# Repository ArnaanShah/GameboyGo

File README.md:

# Gameboy Go 🎮

A handheld console for playing retro games with an interesting sliding mechanism. The console has aspects of a Gameboy and a PSP Go, which led to the name. I made this as a part of [Hackclub's Stasis](https://stasis.hackclub.com) program which funds custom hardware projects. I decided to make a game console because I thought it could teach me a lot of new things and allow me to explore topics I'd been interested in for a long time. It also seemed like it would be very fun, and I could continue using it after I finished the build.

## Setup
### The steps you'll need to get up and running with a Gameboy Go

1. Order all the parts based off the BOM
2. Solder your electrical components onto your PCB based on the models and schematics
3. Download RetroPie using the raspberry pi imager and put it on a SD card into the raspberry pi
4. Use a computer and the command line to get setup and change the configuration files according to the instructions
5. Unplug all components 
6. Assemble the bottom half of the case in this order - Bottom, PCB, Middle, Buttons, Top
7. Assemble the top half of the case containing the screen in this order - Bottom, Display, Top
8. Route the wires to connect the screen to the main case
9. Plug it into a power source
10. You're done!

## Features
### What this console can do and what it's made of

- 2 part sliding black and yellow case
- 3.5 inch screen
- 15 buttons including face buttons, a DPAD, shoulder buttons, menu buttons, and volume controls
- 3.5mm audio jack for headphones

## CAD 
### The 3d model of the case and components

I modeled in fusion 360 but I also got a lot of models for components online. In total, this will require 21 screws and 17 nuts. 7 will be used to hold parts of the case together, 2 will be used for the PCB, and 8 will be used for the hinges. There are 3 separate parts in the main case. The bottom, the middle, and the top. The other portion has 2 parts to sandwich the screen so just a top and bottom. The parts are held together by 4 hinges. The wires for the screen are routed through the back and there is also a hole there for power. 

Images:

## PCB 
### Details about the PCB I made

I made my PCB in KiCad. I used it before for other projects so I already knew the basics. My schematic was pretty simple but included things like a low-pass filter for the audio. The PCB layout was also easy to make but I just had to work around a lot of the constraints with making a PCB of this size with this many components. 

Schematic:

PCB:

3d Renders:

## Software Configuration
### How to get setup with the software and make RetroPie work with this console

There wasn't much to do on the software/programming side of this project. I had planned from the start to use an emulator called RetroPie for the console. It handles almost everything and you just need to set it up and change some things to match your console. 

In order to get RetroPie working on the Gameboy Go, you have to add audio functionality, configure the WaveShare screen, and use RetroGame for button inputs. 

First, get your screen up and running by accessing the pi from your computer and following [these instructions](https://www.waveshare.com/wiki/3.5inch_RPi_LCD_(G)#Calibrate_Resistive_Touch_Screen) from the official wiki. 

Then, add these lines to your config.txt file to get audio on the headphone jack working:
```
dtparam=audio=on

audio_pwm_mode=2
(This may be on by default but if not add it)
```

Finally, for the buttons, you need to [install RetroGame](https://learn.adafruit.com/retro-gaming-with-raspberry-pi/adding-controls-software) from Adafruit in order to convert button inputs from GPIO pins to key presses. Then, you need to edit the retrogame.cfg file to match the one provided in the configuration folder. 

That should be everything needed to get the console running nicely. 

## BOM
### Bill of materials needed with names, links, and quantities

| Name | Amount | Link |
|---|---|---|
| Raspberry pi Zero 2 w | 1 | [Raspberry pi](https://www.raspberrypi.com/products/raspberry-pi-zero-2-w/?variant=raspberry-pi-zero-2-w) |
| 3.5inch RPi LCD (G) | 1 | [WaveShare](https://www.waveshare.com/3.5inch-rpi-lcd-g.htm?srsltid=AfmBOopoyxl4aeTF2s5BtMy4MCuqwqXwdewwnlaeLHAK1Bwd1KD4Ym0p) |
| 6mm Push Buttons | 11 | [Adafruit](https://www.adafruit.com/product/367?srsltid=AfmBOoqAj2fYT_9Y2s0Y7QZpG46cAeABVtzY1UmmWIn-tXu1GYy3M0Tw) |
| 270 ohm resistors | 2 | [MicroCenter](https://www.microcenter.com/product/689184/leo-sales-ltd-resistors-05w-270ohm-metal-oxide-10-pack) |
| 33nF Capacitors  | 2 | [Aliexpress](https://www.aliexpress.us/item/3256806455818371.html?spm=a2g0o.productlist.main.1.157364ba1Yi2YQ&algo_pvid=a6c3f40d-cf68-4b87-af1d-c807c6ebc1ea&algo_exp_id=a6c3f40d-cf68-4b87-af1d-c807c6ebc1ea-0&pdp_ext_f=%7B"order"%3A"526"%2C"eval"%3A"1"%2C"fromPage"%3A"search"%7D&pdp_npi=6%40dis%21USD%212.16%210.99%21%21%2114.67%216.68%21%402101c44517770998316333468e44ca%2112000037902429351%21sea%21US%210%21ABX%211%210%21n_tag%3A-29910%3Bd%3A1deda900%3Bm03_new_user%3A-29895%3BpisId%3A5000000203537349&curPageLogUid=ahvGlUmzWuX5&utparam-url=scene%3Asearch%7Cquery_from%3A%7Cx_object_id%3A1005006642133123%7C_p_origin_prod%3A) |
| M3 Hex Nuts | 17 | [Home Depot](https://www.homedepot.com/p/Everbilt-M3-0-5-Zinc-Hex-Nut-5-Pieces-862798/323368368) |
| M3 Screws | 17 | [Home Depot](https://www.homedepot.com/p/M3-0-5-x-25-mm-Phillips-Pan-Head-Stainless-Steel-Machine-Screw-2-Pack-842748/204283766) |
| M2.5 Screws | 4 | [Home Depot](https://www.homedepot.com/p/Prime-Line-M2-5-0-45-x-10-mm-Zinc-Plated-Steel-Phillips-Drive-Pan-Head-Metric-Machine-Screws-25-Pack-9130848/311229794)|
| Sparkfun 5-way Switch | 1 | [Aliexpress](https://www.aliexpress.us/item/2251832459877116.html?src=google&src=google&albch=shopping&acnt=708-803-3821&isdl=y&slnk=&plac=&mtctp=&albbt=Google_7_shopping&aff_platform=google&aff_short_key=UneMJZVf&gclsrc=aw.ds&albagn=888888&ds_e_adid=&ds_e_matchtype=&ds_e_device=c&ds_e_network=x&ds_e_product_group_id=&ds_e_product_id=en2251832459877116&ds_e_product_merchant_id=107407105&ds_e_product_country=US&ds_e_product_language=en&ds_e_product_channel=online&ds_e_product_store_id=&ds_url_v=2&albcp=19558607238&albag=&isSmbAutoCall=false&needSmbHouyi=false&gad_source=1&gad_campaignid=19566915268&gclid=CjwKCAjwqazPBhALEiwAOuXqdOePMoYkzu9AJ8uqxPdbrhwhWEiKvReEP_qOVmW35NRlWhqx1O2liRoCb6cQAvD_BwE&gatewayAdapt=glo2usa) |
| Sparkfun TRRS Breakout | 1 | [Sparkfun](https://www.sparkfun.com/sparkfun-trrs-3-5mm-jack-breakout.html?gad_source=1&gad_campaignid=17479024039&gclid=CjwKCAjwqazPBhALEiwAOuXqdJmdIlovKzbgYQDtQEwtJ_wsp0qeUwmUB5OWLQOMiqpNB_8F0yb3FhoCtgUQAvD_BwE) |
| 40 Pin Header | 1 | [Adafruit](https://www.adafruit.com/product/2822) |
| 12 Pin Header | 1 | [Aliexpress](https://www.aliexpress.us/item/3256808907494688.html?src=google&src=google&albch=shopping&acnt=708-803-3821&isdl=y&slnk=&plac=&mtctp=&albbt=Google_7_shopping&aff_platform=google&aff_short_key=UneMJZVf&gclsrc=aw.ds&albagn=888888&ds_e_adid=&ds_e_matchtype=&ds_e_device=c&ds_e_network=x&ds_e_product_group_id=&ds_e_product_id=en3256808907494688&ds_e_product_merchant_id=5667405338&ds_e_product_country=US&ds_e_product_language=en&ds_e_product_channel=online&ds_e_product_store_id=&ds_url_v=2&albcp=20123152476&albag=&isSmbAutoCall=false&needSmbHouyi=false&gad_source=1&gad_campaignid=20127768206&gclid=CjwKCAjwqazPBhALEiwAOuXqdN9Pz6WZsAVT2R7mCSNVDfhqV7nhC78X3GVik8dpSUpEzkkHtHR5fBoCjmkQAvD_BwE&gatewayAdapt=glo2usa) |
| 3d printed case and components | 1 | N/A |

## Extras
### Random related things

I made the logo with the help of chat gpt and then edited it in Canva.

These are some photos of my original brainstorming sketches in my notebook:

I think I succesfully made what I originally envisioned in these sketches and I had a lot of fun coming up with them.

This design was inspired a lot by the PSP Go and Gameboy, but also by a build I saw from Marcin Plaza where he made a sliding phone. 

Some changes I could still make -
- Embedding magnets in the case
- Adding a battery
- Improving the shoulder buttons

# Thank you so much for reading and being interested in my project! If you would like to know more feel free to reach out to me. I hope you enjoy what I've made as much as I have.

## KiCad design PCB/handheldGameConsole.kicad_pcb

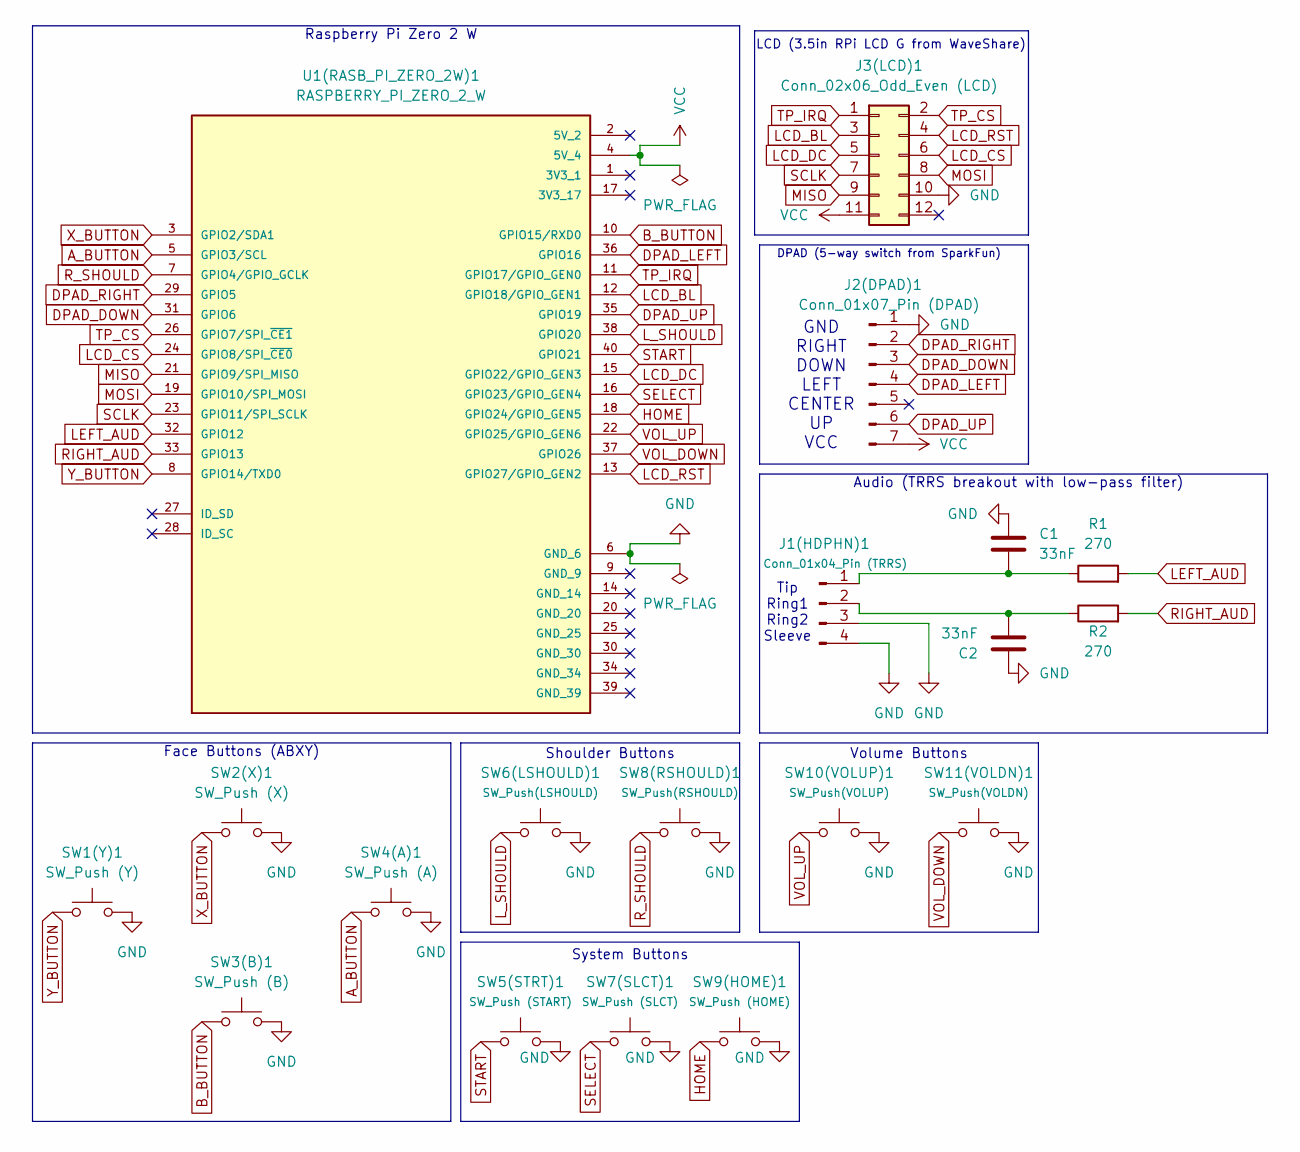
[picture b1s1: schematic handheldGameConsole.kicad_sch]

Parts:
C1, C2: 33nF; C_Disc_D5.0mm_W2.5mm_P5.00mm
J1(HDPHN)1: Conn_01x04_Pin (TRRS); PinHeader_1x04_P2.54mm_Vertical
J2(DPAD)1: Conn_01x07_Pin (DPAD); PinHeader_1x07_P2.54mm_Vertical
J3(LCD)1: Conn_02x06_Odd_Even (LCD); PinHeader_2x06_P2.54mm_Vertical
R1, R2: 270; R_Axial_DIN0207_L6.3mm_D2.5mm_P10.16mm_Horizontal
SW1(Y)1: SW_Push (Y); SW_PUSH_6mm
SW2(X)1: SW_Push (X); SW_PUSH_6mm
SW3(B)1: SW_Push (B); SW_PUSH_6mm
SW4(A)1: SW_Push (A); SW_PUSH_6mm
SW5(STRT)1: SW_Push (START); SW_PUSH_6mm
SW6(LSHOULD)1: SW_Push(LSHOULD); SW_PUSH_6mm
SW7(SLCT)1: SW_Push (SLCT); SW_PUSH_6mm
SW8(RSHOULD)1: SW_Push(RSHOULD); SW_PUSH_6mm
SW9(HOME)1: SW_Push (HOME); SW_PUSH_6mm
SW10(VOLUP)1: SW_Push(VOLUP); SW_PUSH_6mm
SW11(VOLDN)1: SW_Push(VOLDN); SW_PUSH_6mm
U1(RASB_PI_ZERO_2W)1: RASPBERRY_PI_ZERO_2_W; PinHeader_2x20_P2.54mm_Vertical; PARTREV April 2024

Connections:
A_BUTTON: SW4(A)1.1, U1(RASB_PI_ZERO_2W)1.5 (GPIO3/SCL)
B_BUTTON: SW3(B)1.1, U1(RASB_PI_ZERO_2W)1.10 (GPIO15/RXD0)
DPAD_DOWN: J2(DPAD)1.3, U1(RASB_PI_ZERO_2W)1.31 (GPIO6)
DPAD_LEFT: J2(DPAD)1.4, U1(RASB_PI_ZERO_2W)1.36 (GPIO16)
DPAD_RIGHT: J2(DPAD)1.2, U1(RASB_PI_ZERO_2W)1.29 (GPIO5)
DPAD_UP: J2(DPAD)1.6, U1(RASB_PI_ZERO_2W)1.35 (GPIO19)
GND: C1.1, C2.1, J1(HDPHN)1.3, J1(HDPHN)1.4, J2(DPAD)1.1, J3(LCD)1.10, SW1(Y)1.2, SW2(X)1.2, SW3(B)1.2, SW4(A)1.2, SW5(STRT)1.2, SW6(LSHOULD)1.2, SW7(SLCT)1.2, SW8(RSHOULD)1.2, SW9(HOME)1.2, SW10(VOLUP)1.2, SW11(VOLDN)1.2, U1(RASB_PI_ZERO_2W)1.6 (GND_6)
HOME: SW9(HOME)1.1, U1(RASB_PI_ZERO_2W)1.18 (GPIO24/GPIO_GEN5)
LCD_BL: J3(LCD)1.3, U1(RASB_PI_ZERO_2W)1.12 (GPIO18/GPIO_GEN1)
LCD_CS: J3(LCD)1.6, U1(RASB_PI_ZERO_2W)1.24 (GPIO8/SPI_~CE0)
LCD_DC: J3(LCD)1.5, U1(RASB_PI_ZERO_2W)1.15 (GPIO22/GPIO_GEN3)
LCD_RST: J3(LCD)1.4, U1(RASB_PI_ZERO_2W)1.13 (GPIO27/GPIO_GEN2)
LEFT_AUD: R1.2, U1(RASB_PI_ZERO_2W)1.32 (GPIO12)
L_SHOULD: SW6(LSHOULD)1.1, U1(RASB_PI_ZERO_2W)1.38 (GPIO20)
MISO: J3(LCD)1.9, U1(RASB_PI_ZERO_2W)1.21 (GPIO9/SPI_MISO)
MOSI: J3(LCD)1.8, U1(RASB_PI_ZERO_2W)1.19 (GPIO10/SPI_MOSI)
unnamed: C1.2, J1(HDPHN)1.1, R1.1
unnamed: C2.2, J1(HDPHN)1.2, R2.1
RIGHT_AUD: R2.2, U1(RASB_PI_ZERO_2W)1.33 (GPIO13)
R_SHOULD: SW8(RSHOULD)1.1, U1(RASB_PI_ZERO_2W)1.7 (GPIO4/GPIO_GCLK)
SCLK: J3(LCD)1.7, U1(RASB_PI_ZERO_2W)1.23 (GPIO11/SPI_SCLK)
SELECT: SW7(SLCT)1.1, U1(RASB_PI_ZERO_2W)1.16 (GPIO23/GPIO_GEN4)
START: SW5(STRT)1.1, U1(RASB_PI_ZERO_2W)1.40 (GPIO21)
TP_CS: J3(LCD)1.2, U1(RASB_PI_ZERO_2W)1.26 (GPIO7/SPI_~CE1)
TP_IRQ: J3(LCD)1.1, U1(RASB_PI_ZERO_2W)1.11 (GPIO17/GPIO_GEN0)
VCC: J2(DPAD)1.7, J3(LCD)1.11, U1(RASB_PI_ZERO_2W)1.4 (5V_4)
VOL_DOWN: SW11(VOLDN)1.1, U1(RASB_PI_ZERO_2W)1.37 (GPIO26)
VOL_UP: SW10(VOLUP)1.1, U1(RASB_PI_ZERO_2W)1.22 (GPIO25/GPIO_GEN6)
X_BUTTON: SW2(X)1.1, U1(RASB_PI_ZERO_2W)1.3 (GPIO2/SDA1)
Y_BUTTON: SW1(Y)1.1, U1(RASB_PI_ZERO_2W)1.8 (GPIO14/TXD0)

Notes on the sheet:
GND RIGHT DOWN LEFT CENTER UP VCC
Tip Ring1 Ring2 Sleeve
Shoulder Buttons
Volume Buttons
LCD (3.5in RPi LCD G from WaveShare)
Face Buttons (ABXY)
Audio (TRRS breakout with low-pass filter)
DPAD (5-way switch from SparkFun)
System Buttons
Raspberry Pi Zero 2 W

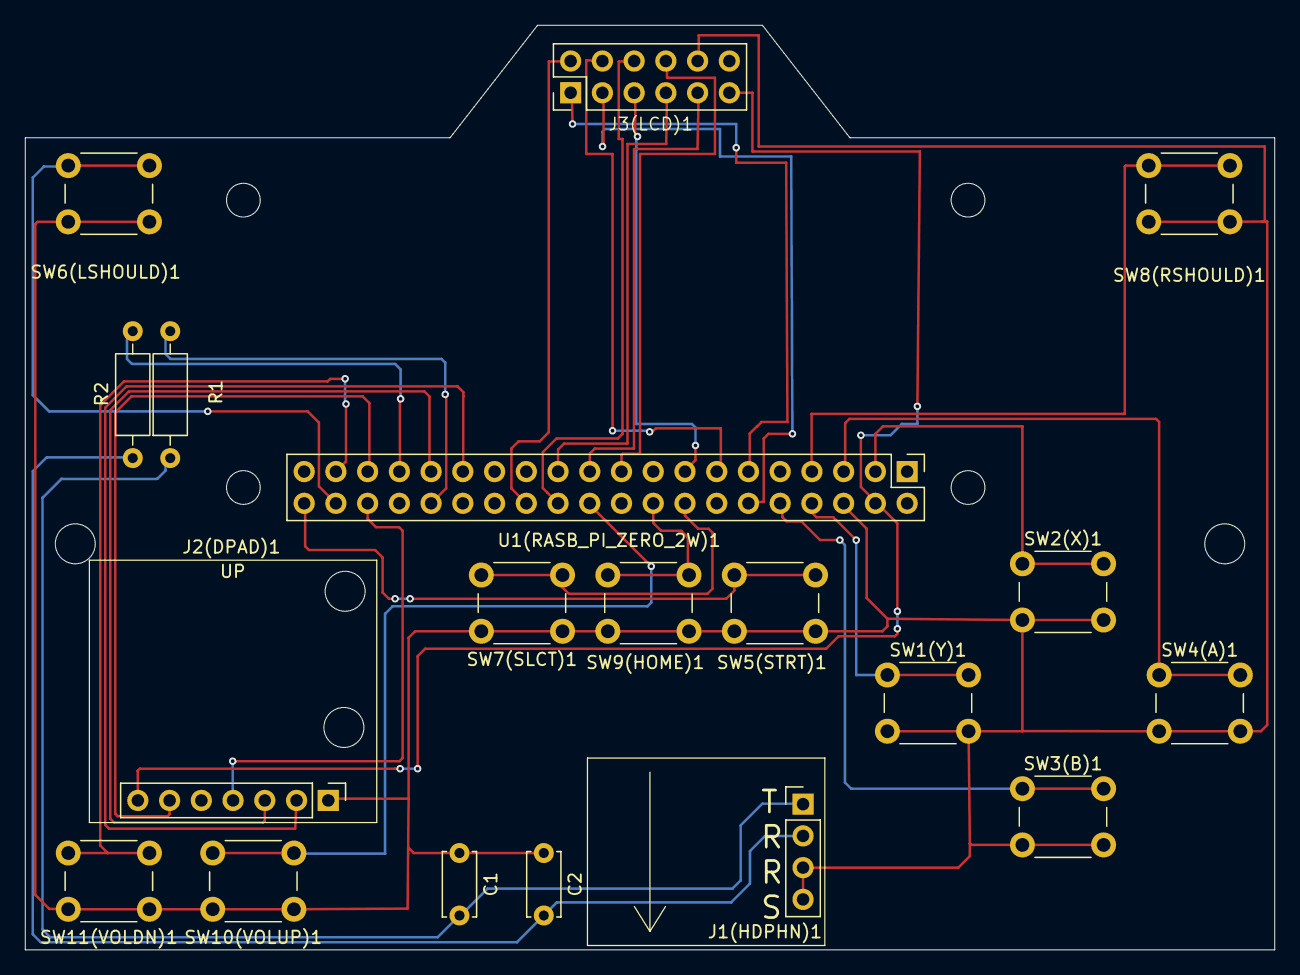
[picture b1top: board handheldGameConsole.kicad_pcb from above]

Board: 2 copper layers, 100.0 x 74.0 mm, 23 parts (0 on the bottom side), 30 nets.

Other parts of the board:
MOUNTING HOLE: MountingHole_3.2mm_M3
MOUNTING HOLE#2, MOUNTING HOLE#3, MOUNTING HOLE#4: MountingHole_3.2mm_M3

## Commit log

2026-04-25 Add all required files
    Added files for PCB, CAD, Operating System, and production.
2026-04-25 Revise README with comprehensive project details
2026-04-25 Create BOM.csv with component details
    Added a Bill of Materials (BOM) with components and links.
